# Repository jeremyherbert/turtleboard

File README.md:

# turtleboard
A USB-enabled STM32F042F6 breakout board.

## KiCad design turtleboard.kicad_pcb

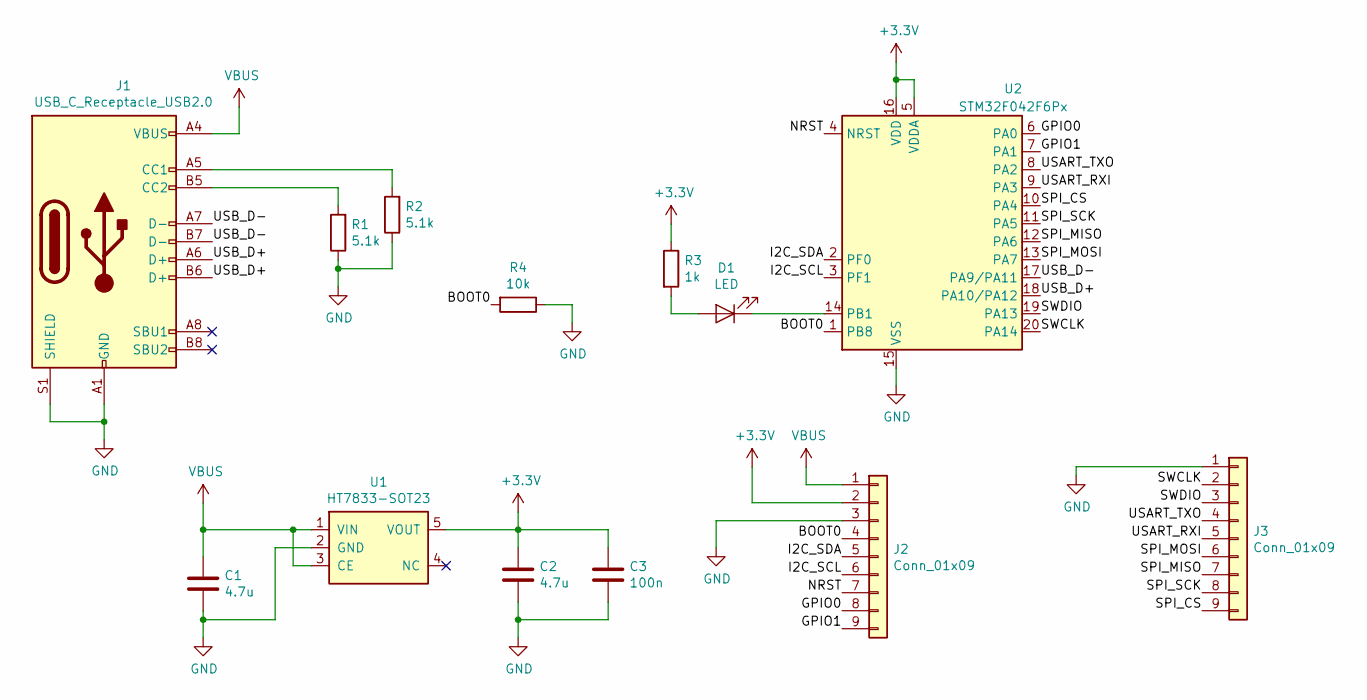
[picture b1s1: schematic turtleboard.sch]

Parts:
C1, C2: 4.7u; C_0805_2012Metric_Pad1.15x1.40mm_HandSolder
C3: 100n; C_0805_2012Metric_Pad1.15x1.40mm_HandSolder
D1: LED; LED_0805_2012Metric_Pad1.15x1.40mm_HandSolder
J1: USB_C_Receptacle_USB2.0; USB_C_Receptacle_Palconn_UTC16-G
J2, J3: Conn_01x09; PinHeader_1x09_P2.54mm_Vertical
R1, R2: 5.1k; R_0805_2012Metric_Pad1.15x1.40mm_HandSolder
R3: 1k; R_0805_2012Metric_Pad1.15x1.40mm_HandSolder
R4: 10k; R_0805_2012Metric_Pad1.15x1.40mm_HandSolder
U1: HT7833-SOT23; SOT-23-5_HandSoldering
U2: STM32F042F6Px; TSSOP-20_4.4x6.5mm_P0.65mm

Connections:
+3V3: C2.1, C3.1, J2.2, R3.1, U1.5 (VOUT), U2.5 (VDDA), U2.16 (VDD)
/BOOT0: J2.4, R4.2, U2.1 (PB8)
/GPIO0: J2.8, U2.6 (PA0)
/GPIO1: J2.9, U2.7 (PA1)
/I2C_SCL: J2.6, U2.3 (PF1)
/I2C_SDA: J2.5, U2.2 (PF0)
/NRST: J2.7, U2.4 (NRST)
/SPI_CS: J3.9, U2.10 (PA4)
/SPI_MISO: J3.7, U2.12 (PA6)
/SPI_MOSI: J3.6, U2.13 (PA7)
/SPI_SCK: J3.8, U2.11 (PA5)
/SWCLK: J3.2, U2.20 (PA14)
/SWDIO: J3.3, U2.19 (PA13)
/USART_RXI: J3.5, U2.9 (PA3)
/USART_TXO: J3.4, U2.8 (PA2)
/USB_D+: J1.A6 (D+), J1.B6 (D+), U2.18 (PA10/PA12)
/USB_D-: J1.A7 (D-), J1.B7 (D-), U2.17 (PA9/PA11)
GND: C1.2, C2.2, C3.2, J1.A1 (GND), J1.A12 (GND), J1.B1 (GND), J1.B12 (GND), J1.S1 (SHIELD), J2.3, J3.1, R1.1, R2.1, R4.1, U1.2 (GND), U2.15 (VSS)
unnamed: D1.1 (K), U2.14 (PB1)
unnamed: D1.2 (A), R3.2
unnamed: J1.A5 (CC1), R2.2
unnamed: J1.B5 (CC2), R1.2
VBUS: C1.1, J1.A4 (VBUS), J1.A9 (VBUS), J1.B4 (VBUS), J1.B9 (VBUS), J2.1, U1.1 (VIN), U1.3 (CE)

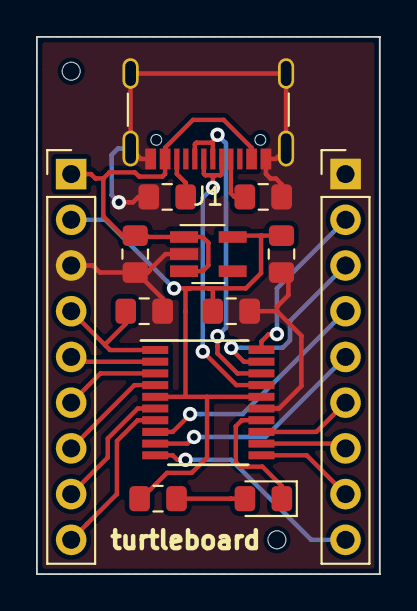
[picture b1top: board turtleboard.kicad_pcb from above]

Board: 2 copper layers, 19.0 x 29.8 mm, 13 parts (0 on the bottom side), 23 nets.

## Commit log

2020-03-09 initial release
